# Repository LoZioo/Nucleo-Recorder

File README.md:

# Nucleo-Recorder
Legacy Nucleo-Recorder project repository.

[Brief documentation](docs/step%202.pdf)

## Final result

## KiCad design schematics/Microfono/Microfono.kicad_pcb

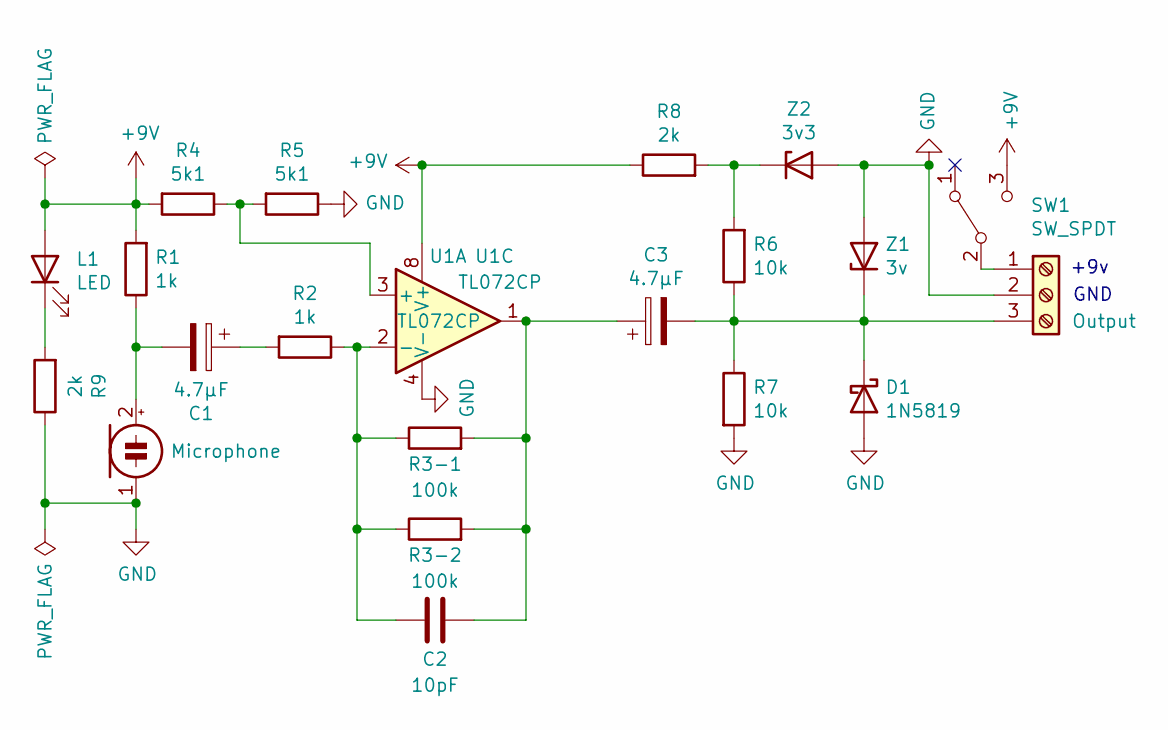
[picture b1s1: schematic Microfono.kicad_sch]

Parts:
C1, C3: 4.7µF; CP_Radial_D4.0mm_P2.00mm
C2: 10pF; C_Disc_D3.0mm_W1.6mm_P2.50mm
D1: 1N5819; D_DO-41_SOD81_P10.16mm_Horizontal
L1: LED; LED_D5.0mm
MIC1: Microphone; CP_Radial_D5.0mm_P2.00mm
O1: Output; PhoenixContact_MSTBVA_2,5_3-G_1x03_P5.00mm_Vertical
R1, R2: 1k; R_Axial_DIN0207_L6.3mm_D2.5mm_P10.16mm_Horizontal
R3-1, R3-2: 100k; R_Axial_DIN0207_L6.3mm_D2.5mm_P10.16mm_Horizontal
R4, R5: 5k1; R_Axial_DIN0207_L6.3mm_D2.5mm_P10.16mm_Horizontal
R6, R7: 10k; R_Axial_DIN0207_L6.3mm_D2.5mm_P10.16mm_Horizontal
R8, R9: 2k; R_Axial_DIN0207_L6.3mm_D2.5mm_P10.16mm_Horizontal
SW1: SW_SPDT; SW_Slide_1P2T_CK_OS102011MS2Q
U1: TL072CP; DIP-8_W7.62mm_Socket
Z1: 3v; D_DO-34_SOD68_P7.62mm_Horizontal
Z2: 3v3; D_DO-34_SOD68_P7.62mm_Horizontal

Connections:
+9V: L1.2 (A), R1.2, R4.2, R8.1, SW1.3 (C), U1.8 (V+); also elsewhere on the board
GND: D1.2 (A), MIC1.1 (-), O1.2, R5.1, R7.2, R9.1, U1.4 (V-), Z1.2 (A), Z2.2 (A)
unnamed: C1.1, R2.2
unnamed: C1.2, MIC1.2 (+), R1.1
unnamed: C2.1, R2.1, R3-1.1, R3-2.1, U1.2 (-)
unnamed: C2.2, C3.1, R3-1.2, R3-2.2, U1.1
unnamed: C3.2, D1.1 (K), O1.3, R6.1, R7.1, Z1.1 (K)
unnamed: L1.1 (K), R9.2
unnamed 8: O1.1, SW1.2 (B); also elsewhere on the board
unnamed: R4.1, R5.2, U1.3 (+)
unnamed: R6.2, R8.2, Z2.1 (K)

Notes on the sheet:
+9v
GND

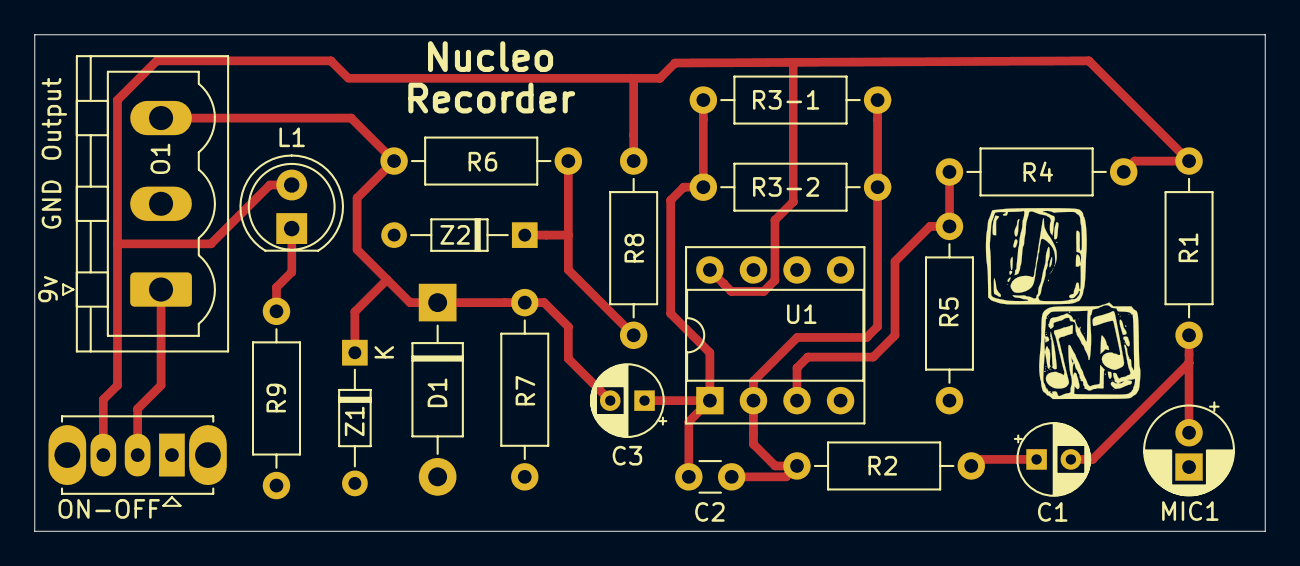
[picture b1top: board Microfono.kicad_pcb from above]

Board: 2 copper layers, 71.8 x 29.0 mm, 21 parts (0 on the bottom side), 11 nets.

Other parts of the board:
ON-OFF: SW_SPDT; SW_Slide_1P2T_CK_OS102011MS2Q

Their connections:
+9V: ON-OFF.3; also elsewhere on the board
unnamed 8: ON-OFF.2; also elsewhere on the board

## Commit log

2023-10-05 First commit.
2023-10-05 docs
